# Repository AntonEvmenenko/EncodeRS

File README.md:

# EncodeRS

**A dirt-cheap, minimal-component RS485 magnetic encoder designed to sit right on the back of a Nema 17 stepper motor.**

Building a closed-loop stepper system or a FOC (Field Oriented Control) setup? This board gives you high-speed, noise-immune angle data without breaking the bank. By using RS485, it ignores the nasty electromagnetic interference (EMI) generated by the motor coils, even over long cables.

## Key Features
*   **Ultra-Low Cost:** Designed with minimal BOM in mind. No fancy or redundant components.
*   **Hand-Assembly Friendly:** SMD components smaller than 0805 were avoided wherever possible, so you don't need eagle eyes or a microscope to build it yourself.
*   **Noise Immune:** RS485 differential signaling ensures your angle data survives the electrically noisy environment right next to a spinning motor.
*   **4-Wire Interface:** Just provide `+5V`, `GND`, and the `A`/`B` differential pair. 
*   **FOC Ready:** Offloads the motor position sensing from the main controller.

## Under the Hood
*   **Sensor:** `MT6816CT-ACD` – SPI magnetic angle sensor.
*   **MCU:** `STM8S003F3P` – Reads the SPI sensor and spits out UART.
*   **Transceiver:** `SP3485EN` – Converts UART to robust RS485.
*   **LDO:** `HT75R33-1A` – Drops the incoming 5V to a clean 3.3V for the logic.

## Project Status
- [x] Schematic design
- [x] PCB routing
- [ ] Enclosure design
- [ ] Firmware development
- [ ] Testing on a real motor under heavy load

## Acknowledgments
A big shoutout to [**dVNaNt**](https://github.com/dVNaNt) for coming up with the perfect name for this project!

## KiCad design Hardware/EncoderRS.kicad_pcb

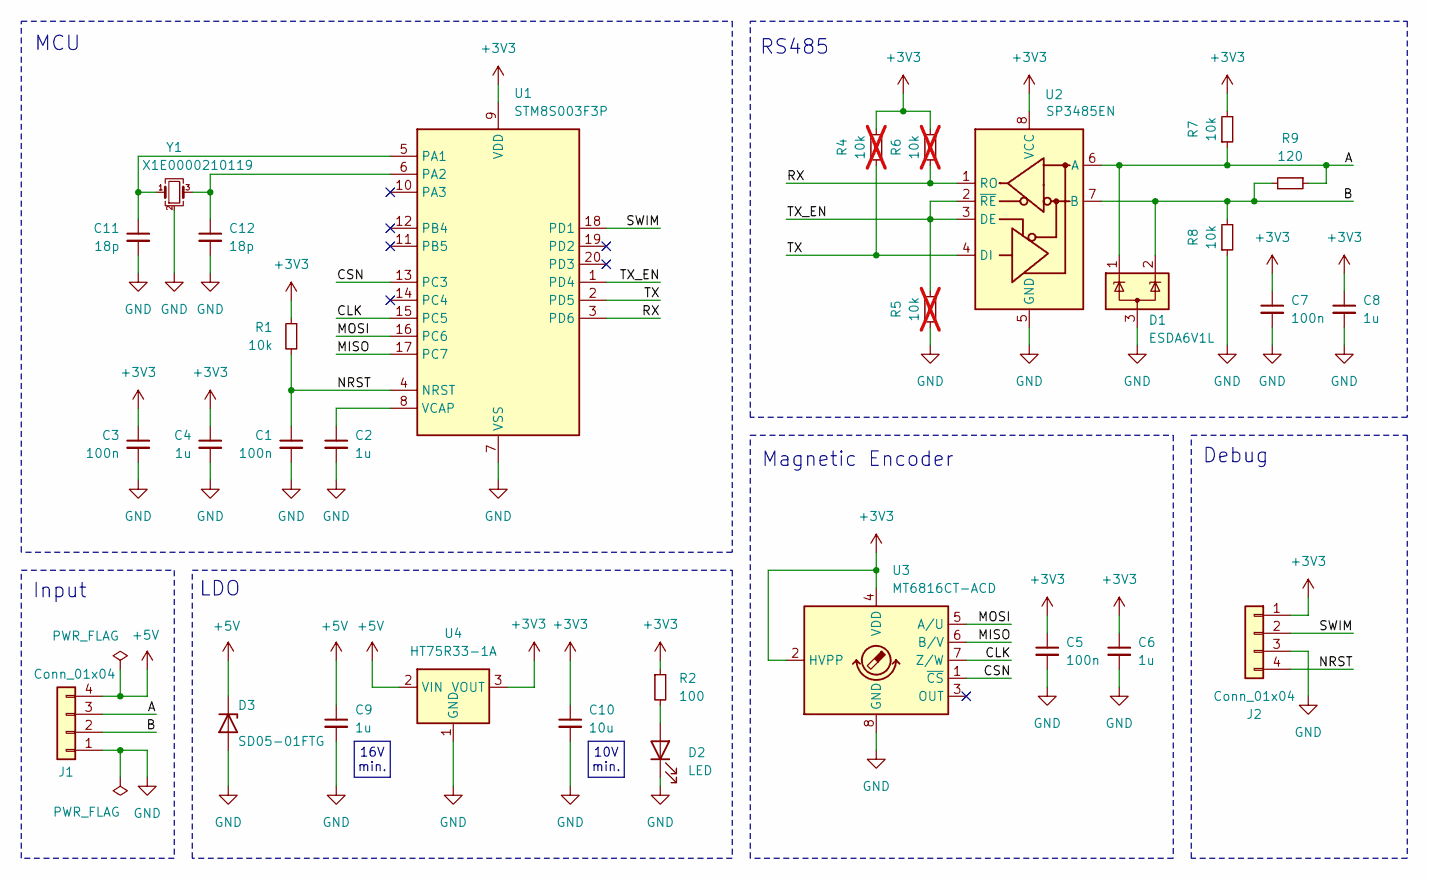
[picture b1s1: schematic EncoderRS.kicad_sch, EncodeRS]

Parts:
C1, C3, C5, C7: 100n; C_0805_2012Metric; LCSC Part Number C16195242
C2, C4, C6, C8, C9: 1u; C_0805_2012Metric; LCSC Part Number C24123
C10: 10u; C_0805_2012Metric; LCSC Part Number C32635
C11, C12: 18p; C_0805_2012Metric; LCSC Part Number C597363
D1: ESDA6V1L; SOT-23-3; LCSC Part Number C24378
D2: LED; LED_1206_3216Metric_ReverseMount_Hole2.1mm; LCSC Part Number C19171367
D3: SD05-01FTG; D_SOD-323_HandSoldering; LCSC Part Number C151235
J1: Conn_01x04; JST_PH_S4B-PH-K_1x04_P2.00mm_Horizontal; LCSC Part Number C157926
J2: Conn_01x04; PinHeader_1x04_P2.54mm_Vertical; LCSC Part Number C160334
R1, R7, R8: 10k; R_0805_2012Metric; LCSC Part Number C4336117
R2: 100; R_0805_2012Metric; LCSC Part Number C859139
R4, R5, R6: 10k; R_0805_2012Metric; LCSC Part Number C4336117; not fitted
R9: 120; R_0805_2012Metric; LCSC Part Number C114244
U1: STM8S003F3P; TSSOP-20_4.4x6.5mm_P0.65mm; LCSC Part Number C52717
U2: SP3485EN; SOIC-8_3.9x4.9mm_P1.27mm; LCSC Part Number C8963
U3: MT6816CT-ACD; SO-8_3.9x4.9mm_P1.27mm; LCSC Part Number C5449395
U4: HT75R33-1A; SOT-23-5; LCSC Part Number C54556441
Y1: X1E0000210119; Crystal_SMD_3225-4Pin_3.2x2.5mm; LCSC Part Number C89371

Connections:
+3V3: C3.1, C4.1, C5.1, C6.1, C7.1, C8.1, C10.1, J2.1, R1.1, R2.1, R4.2, R6.2, R7.2, U1.9 (VDD), U2.8 (VCC), U3.2 (HVPP), U3.4 (VDD), U4.3 (VOUT)
+5V: C9.1, D3.1 (K), J1.4, U4.2 (VIN)
/A: D1.1 (K), J1.3, R7.1, R9.1, U2.6 (A)
/B: D1.2 (K), J1.2, R8.2, R9.2, U2.7 (B)
/CLK: U1.15 (PC5), U3.7 (Z/W)
/CSN: U1.13 (PC3), U3.1 (~CS)
/MISO: U1.17 (PC7), U3.6 (B/V)
/MOSI: U1.16 (PC6), U3.5 (A/U)
/NRST: C1.1, J2.4, R1.2, U1.4 (NRST)
/RX: R6.1, U1.3 (PD6), U2.1 (RO)
/SWIM: J2.2, U1.18 (PD1)
/TX: R4.1, U1.2 (PD5), U2.4 (DI)
/TX_EN: R5.2, U1.1 (PD4), U2.2 (~RE), U2.3 (DE)
GND: C1.2, C2.2, C3.2, C4.2, C5.2, C6.2, C7.2, C8.2, C9.2, C10.2, C11.2, C12.2, D1.3 (A), D2.1 (K), D3.2 (A), J1.1, J2.3, R5.1, R8.1, U1.7 (VSS), U2.5 (GND), U3.8 (GND), U4.1 (GND), Y1.2 (G), Y1.4 (G)
unnamed: D2.2 (A), R2.2
unnamed: C11.1, U1.5 (PA1), Y1.1
unnamed: C12.1, U1.6 (PA2), Y1.3
unnamed: C2.1, U1.8 (VCAP)

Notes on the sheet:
Magnetic Encoder
MCU
LDO
RS485
Debug
Input
16V min.
10V min.

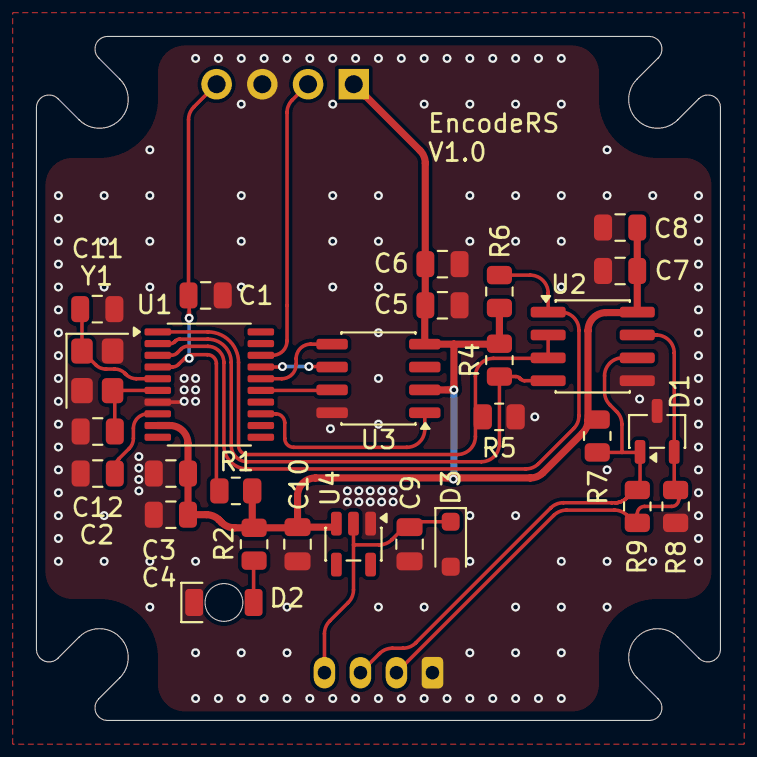
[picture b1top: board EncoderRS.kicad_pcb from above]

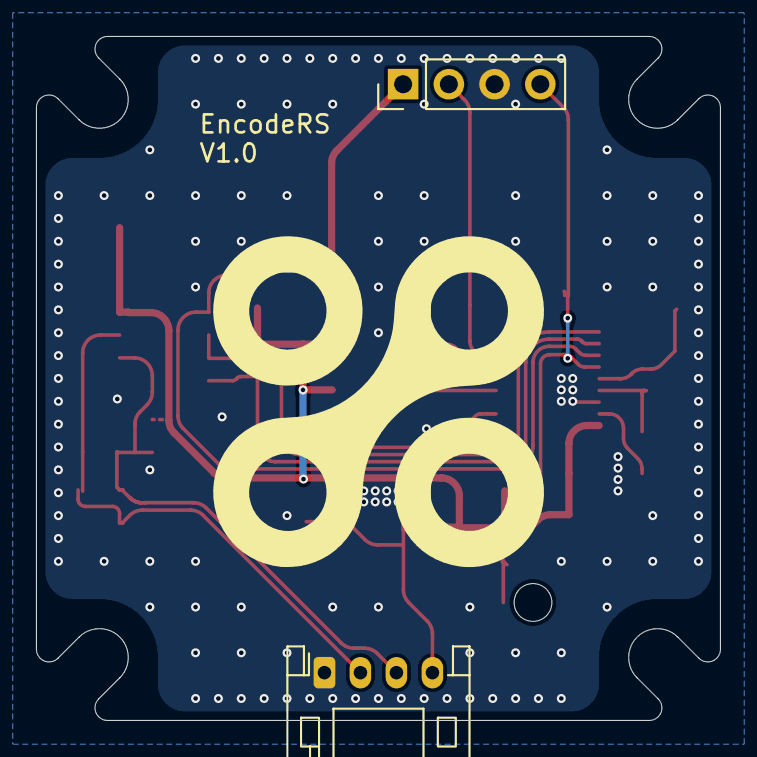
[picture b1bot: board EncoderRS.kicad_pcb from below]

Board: 2 copper layers, 38.0 x 38.0 mm, 30 parts (2 on the bottom side), 18 nets.
